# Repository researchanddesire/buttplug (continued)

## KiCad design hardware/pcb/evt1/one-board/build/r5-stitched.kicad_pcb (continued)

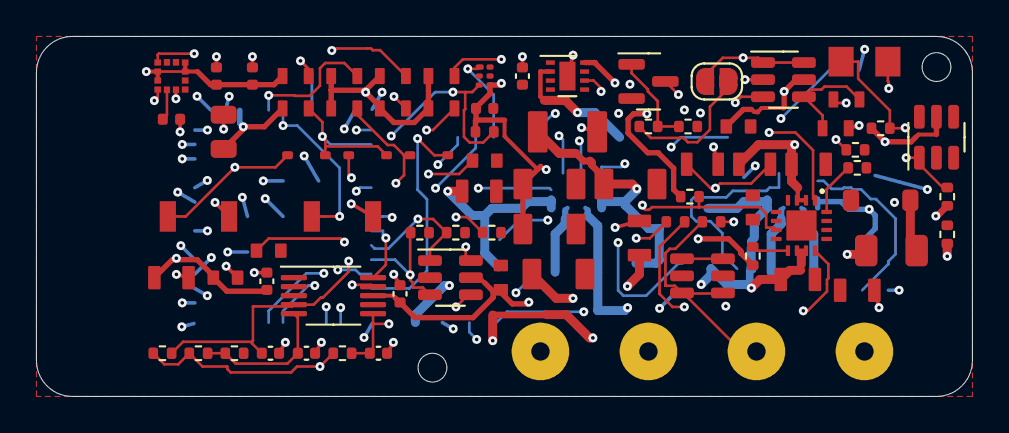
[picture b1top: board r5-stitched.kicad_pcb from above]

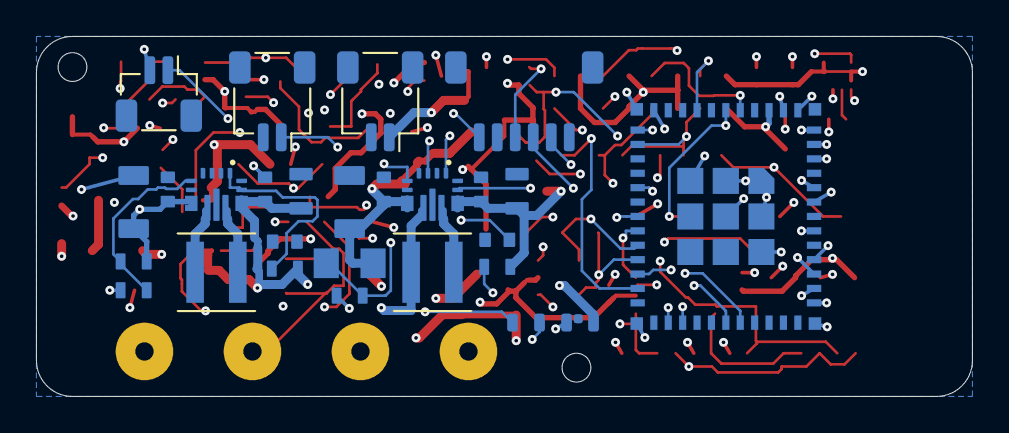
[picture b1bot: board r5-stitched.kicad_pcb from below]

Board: 4 copper layers, 52.0 x 20.0 mm, 110 parts (26 on the bottom side), 55 nets.

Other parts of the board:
J8: PACK MONITOR NTC / GND; JST_SH_SM02B-SRSS-TB_1x02-1MP_P1.00mm_Horizontal
MH1, MH3: PROVISIONAL M1.4 support

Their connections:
GND: J8.2; also elsewhere on the board
PACK_MON_NTC: J8.1; also elsewhere on the board

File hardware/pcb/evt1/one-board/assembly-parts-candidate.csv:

Comment,Designator,Footprint,Manufacturer Part Number,Baseline MPN
4.7uF 16V X7R,C1,Murata_GRM21_0805_Reflow,GRM21BR71C475KE51L,GRM21BR71A475KA73L
4.7uF 16V X7R,C2,Murata_GRM21_0805_Reflow,GRM21BR71C475KE51L,GRM21BR71A475KA73L
4.7uF 16V X7R,C3,Murata_GRM21_0805_Reflow,GRM21BR71C475KE51L,GRM21BR61A106KE19L
10uF 10V,C11,Murata_GRM21_0805_Reflow,GRM21BR61A106KE19L,GRM21BR61A106KE19L
22uF 10V X7R,C13,Murata_GRM31_1206_Reflow,GRM31CR71A226KE15L,GRM31CR71A226KE15L
22uF 10V X7R,C14,Murata_GRM31_1206_Reflow,GRM31CR71A226KE15L,GRM31CR71A226KE15L
22uF 10V X7R,C15,Murata_GRM31_1206_Reflow,GRM31CR71A226KE15L,GRM31CR71A226KE15L
100nF 10V,C16,Murata_GRM18_0603_Reflow,GRM188R71C104KA01D,GRM188R71C104KA01D
10uF 10V X5R 0603 HF,C51,TDK_C1608_0603_Reflow,CL10A106KP8NNNC,C1608X5R1A106K080AC
10uF 10V X5R 0603 HF,C52,TDK_C1608_0603_Reflow,CL10A106KP8NNNC,C1608X5R1A106K080AC
1.5uH / Isat>=4A candidate,L1,L_Coilcraft_XxL4020,XFL4020-152MEC,XFL4020-152MEC
8.87k 1% / ~100mA,R1,R_0402_1005Metric,TC0210B8871TCC,TNPW04028K87BEED
3.24k 1%,R2,R_0402_1005Metric,RT0402BRD073K24L,TNPW04023K24BEED
10k,R3,R_0402_1005Metric,TNPW040210K0BEED,TNPW040210K0BEED
10k,R4,R_0402_1005Metric,TNPW040210K0BEED,TNPW040210K0BEED
10k,R5,R_0402_1005Metric,TNPW040210K0BEED,TNPW040210K0BEED
312k 0.1%,R11,Vishay_TNPW0603_IEC_Reflow,RT0603BRD07312KL,TNPW0603312KBEEA
100k 0.1%,R12,Vishay_TNPW0603_IEC_Reflow,TNPW0603100KBEEA,TNPW0603100KBEEA
10k,R13,Vishay_TNPW0603_IEC_Reflow,TNPW060310K0BEEA,TNPW060310K0BEEA
BQ24074RGT candidate,U1,TI_RGT0016C_3x3mm_BQ24074_EP1.68mm,BQ24074RGTR,BQ24074RGTR
TPS63070RNM candidate,U2,TI_RNM0015A_2.5x3mm_TPS63070,TPS63070RNMR,TPS63070RNMR
10uF 10V,C31,Murata_GRM21_0805_Reflow,GRM21BR61A106KE19L,GRM21BR61A106KE19L
100nF,C32,Murata_GRM18_0603_Reflow,GRM188R71C104KA01D,GRM188R71C104KA01D
1uF,C33,TDK_C1608_0603_Reflow,CGA3E1X7R1V105KT000N,C1608X7R1E105K080AB
100nF,C34,Murata_GRM18_0603_Reflow,GRM188R71C104KA01D,GRM188R71C104KA01D
SERVICE_USB_BOOT,J4,JST_SH_SM06B-SRSS-TB_1x06-1MP_P1.00mm_Horizontal,SM06B-SRSS-TB(LF)(SN),SM06B-SRSS-TB(LF)(SN)
10k,R31,Vishay_TNPW0603_IEC_Reflow,TNPW060310K0BEEA,TNPW060310K0BEEA
10k,R32,Vishay_TNPW0603_IEC_Reflow,TNPW060310K0BEEA,TNPW060310K0BEEA
10k,R33,Vishay_TNPW0603_IEC_Reflow,TNPW060310K0BEEA,TNPW060310K0BEEA
10k,R34,Vishay_TNPW0603_IEC_Reflow,TNPW060310K0BEEA,TNPW060310K0BEEA
10k,R35,Vishay_TNPW0603_IEC_Reflow,TNPW060310K0BEEA,TNPW060310K0BEEA
10k,R36,Vishay_TNPW0603_IEC_Reflow,TNPW060310K0BEEA,TNPW060310K0BEEA
4.7k,R37,Vishay_TNPW0603_IEC_Reflow,TNPW06034K70BEEA,TNPW06034K70BEEA
4.7k,R38,Vishay_TNPW0603_IEC_Reflow,TNPW06034K70BEEA,TNPW06034K70BEEA
1.00M 1%,R39,Vishay_TNPW0805_IEC_Reflow,TNPW08051M00BEEA,TNPW08051M00BEEA
1.00M 1%,R40,Vishay_TNPW0805_IEC_Reflow,TNPW08051M00BEEA,TNPW08051M00BEEA
POWER / momentary,SW1,SW_SPST_B3U-1000P,B3U-1000P,B3U-1000P
MODE / momentary,SW2,SW_SPST_B3U-1000P,B3U-1000P,B3U-1000P
ESP32-C3-MINI-1-H4X,U6,Espressif_ESP32-C3-MINI-1_53Pads,ESP32-C3-MINI-1-H4X,ESP32-C3-MINI-1-N4X
100nF,C43,Murata_GRM18_0603_Reflow,GRM188R71C104KA01D,GRM188R71C104KA01D
100nF,C44,Murata_GRM18_0603_Reflow,GRM188R71C104KA01D,GRM188R71C104KA01D
AO3400A,Q1,SOT-23,AO3400A,AO3400A
10.0k 0.1%,R42,R_0402_1005Metric,TNPW040210K0BEED,TNPW040210K0BEED
715k 0.1%,R43,RESI_PTFR0805_C16003,PTFR0805B715KP9,TNPW0805715KBEEA
110k 0.1%,R44,Vishay_TNPW0603_IEC_Reflow,TNPW0603110KBEEA,TNPW0603110KBEEA
200k 0.1%,R45,Vishay_TNPW0603_IEC_Reflow,ERA3AEB204V,TNPW0603200KBEEA
11k 1%,R46,R_0402_1005Metric,RT0402BRD0711KL,TNPW040211K0BEED
1k 1%,R47,R_0402_1005Metric,TNPW04021K00BEED,TNPW04021K00BEED
100k 1%,R48,R_0402_1005Metric,TNPW0402100KBEED,TNPW0402100KBEED
TPS3700DDCR,U8,TSOT-23-6,TPS3700DDCR,TPS3700DDCR
TPS3808G33QDBVRQ1,U9,SOT-23-6,TPS3808G33QDBVRQ1,TPS3808G33DBVR
100nF,C71,C_0402_1005Metric,GRM155R71C104KA88D,GRM155R71C104KA88D
BAT54WS-E3-08,D71,D_SOD-323,BAT54WS-E3-08,BAT54WS-E3-08
BAT54WS-E3-08,D72,D_SOD-323,BAT54WS-E3-08,BAT54WS-E3-08
BAT54WS-E3-08,D73,D_SOD-323,BAT54WS-E3-08,BAT54WS-E3-08
10k,R71,R_0402_1005Metric,TNPW040210K0BEED,TNPW040210K0BEED
TPS3422EGDRYR,U71,Texas_USON-6_1x1.45mm_P0.5mm_SMD,TPS3422EGDRYR,TPS3422EGDRYR
10uF 10V,C21,Murata_GRM21_0805_Reflow,GRM21BR61A106KE19L,GRM21BR61A106KE19L
22uF 10V X7R,C23,Murata_GRM31_1206_Reflow,GRM31CR71A226KE15L,GRM31CR71A226KE15L
22uF 10V X7R,C24,Murata_GRM31_1206_Reflow,GRM31CR71A226KE15L,GRM31CR71A226KE15L
22uF 10V X7R,C25,Murata_GRM31_1206_Reflow,GRM31CR71A226KE15L,GRM31CR71A226KE15L
100nF 10V,C26,Murata_GRM18_0603_Reflow,GRM188R71C104KA01D,GRM188R71C104KA01D
100nF,C27,Murata_GRM18_0603_Reflow,GRM188R71C104KA01D,GRM188R71C104KA01D
100nF,C28,C_0402_1005Metric,GRM155R71C104KA88D,GRM155R71C104KA88D
100nF,C29,C_0402_1005Metric,GRM155R71C104KA88D,GRM155R71C104KA88D
47uF 10V,C30,Murata_GRM32_1210_Reflow,GRM32ER61A476KE20L,GRM32ER61A476KE20L
10uF 10V X5R 0603 HF,C53,TDK_C1608_0603_Reflow,CL10A106KP8NNNC,C1608X5R1A106K080AC
10uF 10V X5R 0603 HF,C54,TDK_C1608_0603_Reflow,CL10A106KP8NNNC,C1608X5R1A106K080AC
MOTOR_2PIN,J3,JST_SH_SM02B-SRSS-TB_1x02-1MP_P1.00mm_Horizontal,SM02B-SRSS-TB(LF)(SN),SM02B-SRSS-TB(LF)(SN)
1.5uH / Isat>=4A candidate,L2,L_Coilcraft_XxL4020,XFL4020-152MEC,XFL4020-152MEC
360k 0.1%,R21,RESI_PTFR0805_C16003,PTFR0805B360KN9,TNPW0805362KBEEA
100k 0.1%,R22,Vishay_TNPW0603_IEC_Reflow,TNPW0603100KBEEA,TNPW0603100KBEEA
100k,R23,R_0402_1005Metric,TNPW0402100KBEED,TNPW0402100KBEED
100k,R24,R_0402_1005Metric,TNPW0402100KBEED,TNPW0402100KBEED
100k,R25,R_0402_1005Metric,TNPW0402100KBEED,TNPW0402100KBEED
10k,R26,Vishay_TNPW0603_IEC_Reflow,TNPW060310K0BEEA,TNPW060310K0BEEA
TPS63070RNM candidate,U3,TI_RNM0015A_2.5x3mm_TPS63070,TPS63070RNMR,TPS63070RNMR
SN74LVC1G11DBV candidate,U4,SOT-23-6,SN74LVC1G11DBVR,SN74LVC1G11DBVR
DRV8212DSG candidate,U5,WSON-8-1EP_2x2mm_P0.5mm_EP0.9x1.6mm,DRV8212DSGR,DRV8212DSGR
100nF,C61,C_0402_1005Metric,GRM155R71C104KA88D,GRM155R71C104KA88D
10nF,C62,C_0402_1005Metric,GRM155R71H103KA88D,GRM155R71H103KA88D
10nF,C63,C_0402_1005Metric,GRM155R71H103KA88D,GRM155R71H103KA88D
10nF 50V X7R,C88,C_0402_1005Metric,GRM155R71H103KA88D,
TIP NTC / GND,J5,JST_SH_BM02B-SRSS-TB_1x02-1MP_P1.00mm_Vertical,BM02B-SRSS-TB(LF)(SN),BM02B-SRSS-TB(LF)(SN)
PACK MONITOR NTC / GND,J8,JST_SH_SM02B-SRSS-TB_1x02-1MP_P1.00mm_Horizontal,SM02B-SRSS-TB(LF)(SN),
10k 0.1%,R61,R_0402_1005Metric,TNPW040210K0BEED,TNPW040210K0BEED
10k 0.1%,R62,R_0402_1005Metric,TNPW040210K0BEED,TNPW040210K0BEED
10k 0.1%,R63,R_0402_1005Metric,TNPW040210K0BEED,TNPW040210K0BEED
10k 0.1%,R88,R_0402_1005Metric,TNPW040210K0BEED,
ADS1115IDGSR /0x48,U7,VSSOP-10_3x3mm_P0.5mm,ADS1115IDGSR,ADS1115IDGSR
Schottky 1A/20V candidate,D1,Diodes_B140HW_SOD123_A1_K2,B140HW-7,B140HW-7
PTC 500mA candidate,F1,Fuse_1206_3216Metric,1206L050YR,1206L050YR
22R,R75,R_0402_1005Metric,RC0402FR-0722RL,TNPW040222R0BEED
22R,R76,R_0402_1005Metric,RC0402FR-0722RL,TNPW040222R0BEED
USBLC6-2SC6,U75,SOT-23-6,USBLC6-2SC6,USBLC6-2SC6
220nF,C81,C_0402_1005Metric,GRM155R71C224KA12D,GRM155R71C224KA12D
100nF,C82,C_0402_1005Metric,GRM155R71C104KA88D,GRM155R71C104KA88D
47uF 10V / Ceff>=10uF at3V3,C83,C_0805_2012Metric,MSASL21GBB5476MTNA01,C2012X5R1E226M125AC
100nF / VDDIO local,C84,C_0402_1005Metric,GRM155R71C104KA88D,GRM155R71C104KA88D
LSM303AGRTR,U81,LGA-12_2x2mm_P0.5mm,LSM303AGRTR,LSM303AGRTR

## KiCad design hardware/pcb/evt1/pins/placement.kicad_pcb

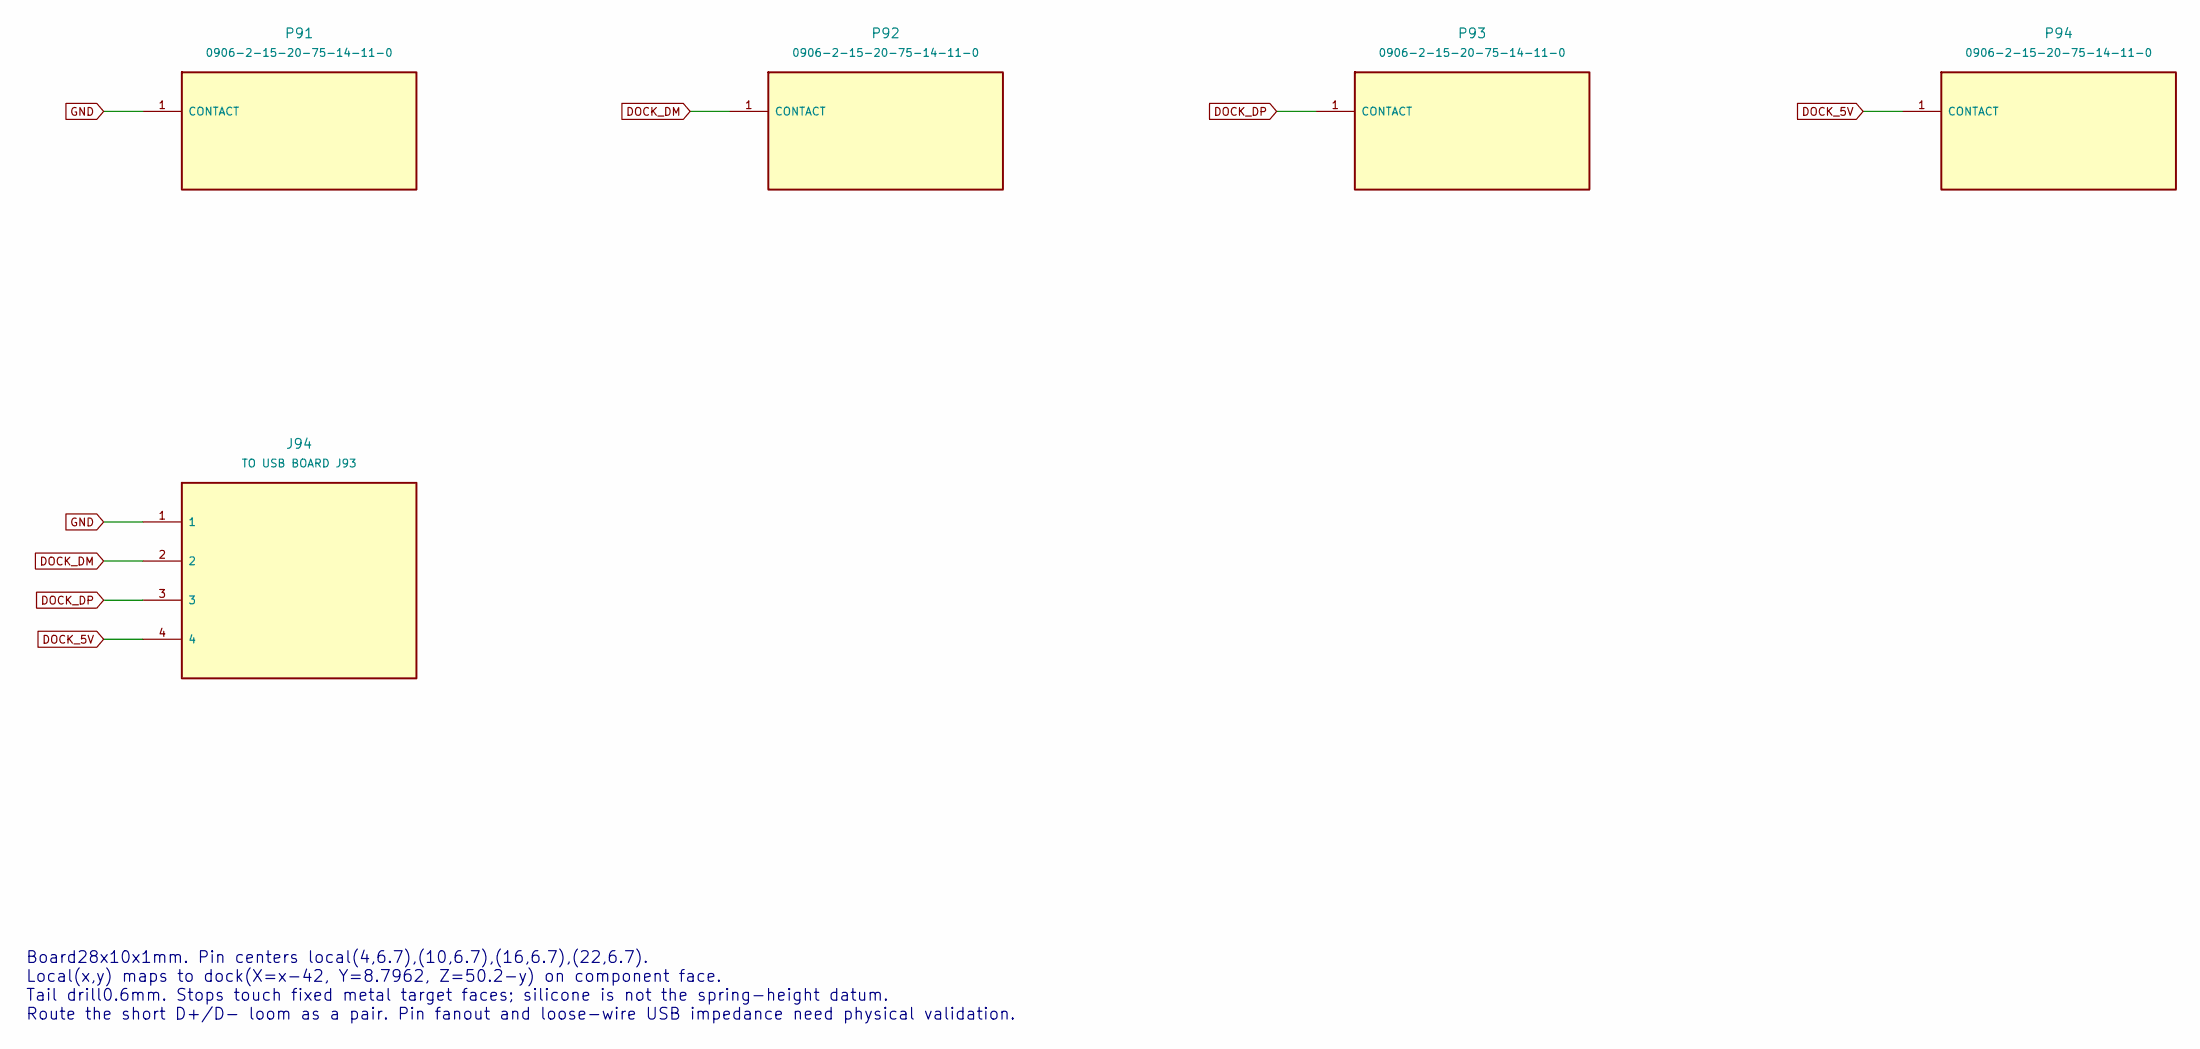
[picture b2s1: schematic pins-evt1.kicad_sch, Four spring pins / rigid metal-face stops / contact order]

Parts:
J94: TO USB BOARD J93; Contact_Loom_4Land
P91, P92, P93, P94: 0906-2-15-20-75-14-11-0; MillMax_0906_2

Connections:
DOCK_5V: J94.4, P94.1
DOCK_DM: J94.2, P92.1
DOCK_DP: J94.3, P93.1
GND: J94.1, P91.1

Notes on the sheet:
Board28x10x1mm. Pin centers local(4,6.7),(10,6.7),(16,6.7),(22,6.7). Local(x,y) maps to dock(X=x-42, Y=8.7962, Z=50.2-y) on component face. Tail drill0.6mm. Stops touch fixed metal target faces; silicone is not the spring-height datum. Route the short D+/D- loom as a pair. Pin fanout and loose-wire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

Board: 2 copper layers, 5 parts (1 on the bottom side), 4 nets, no tracks yet.

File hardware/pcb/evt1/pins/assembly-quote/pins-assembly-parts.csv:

Manufacturer,MPN,Quantity_per_board,References,Schematic_value,Footprint,Assembly_note,Manufacturer_source
Mill-Max,0906-2-15-20-75-14-11-0,4,P91 P92 P93 P94,0906-2-15-20-75-14-11-0,EVT1:MillMax_0906_2,"Spring pin through1mm board; height/stroke are set by the carrier/retainer, not a generic component-height box.",https://www.mill-max.com/products/spring-loaded/0906

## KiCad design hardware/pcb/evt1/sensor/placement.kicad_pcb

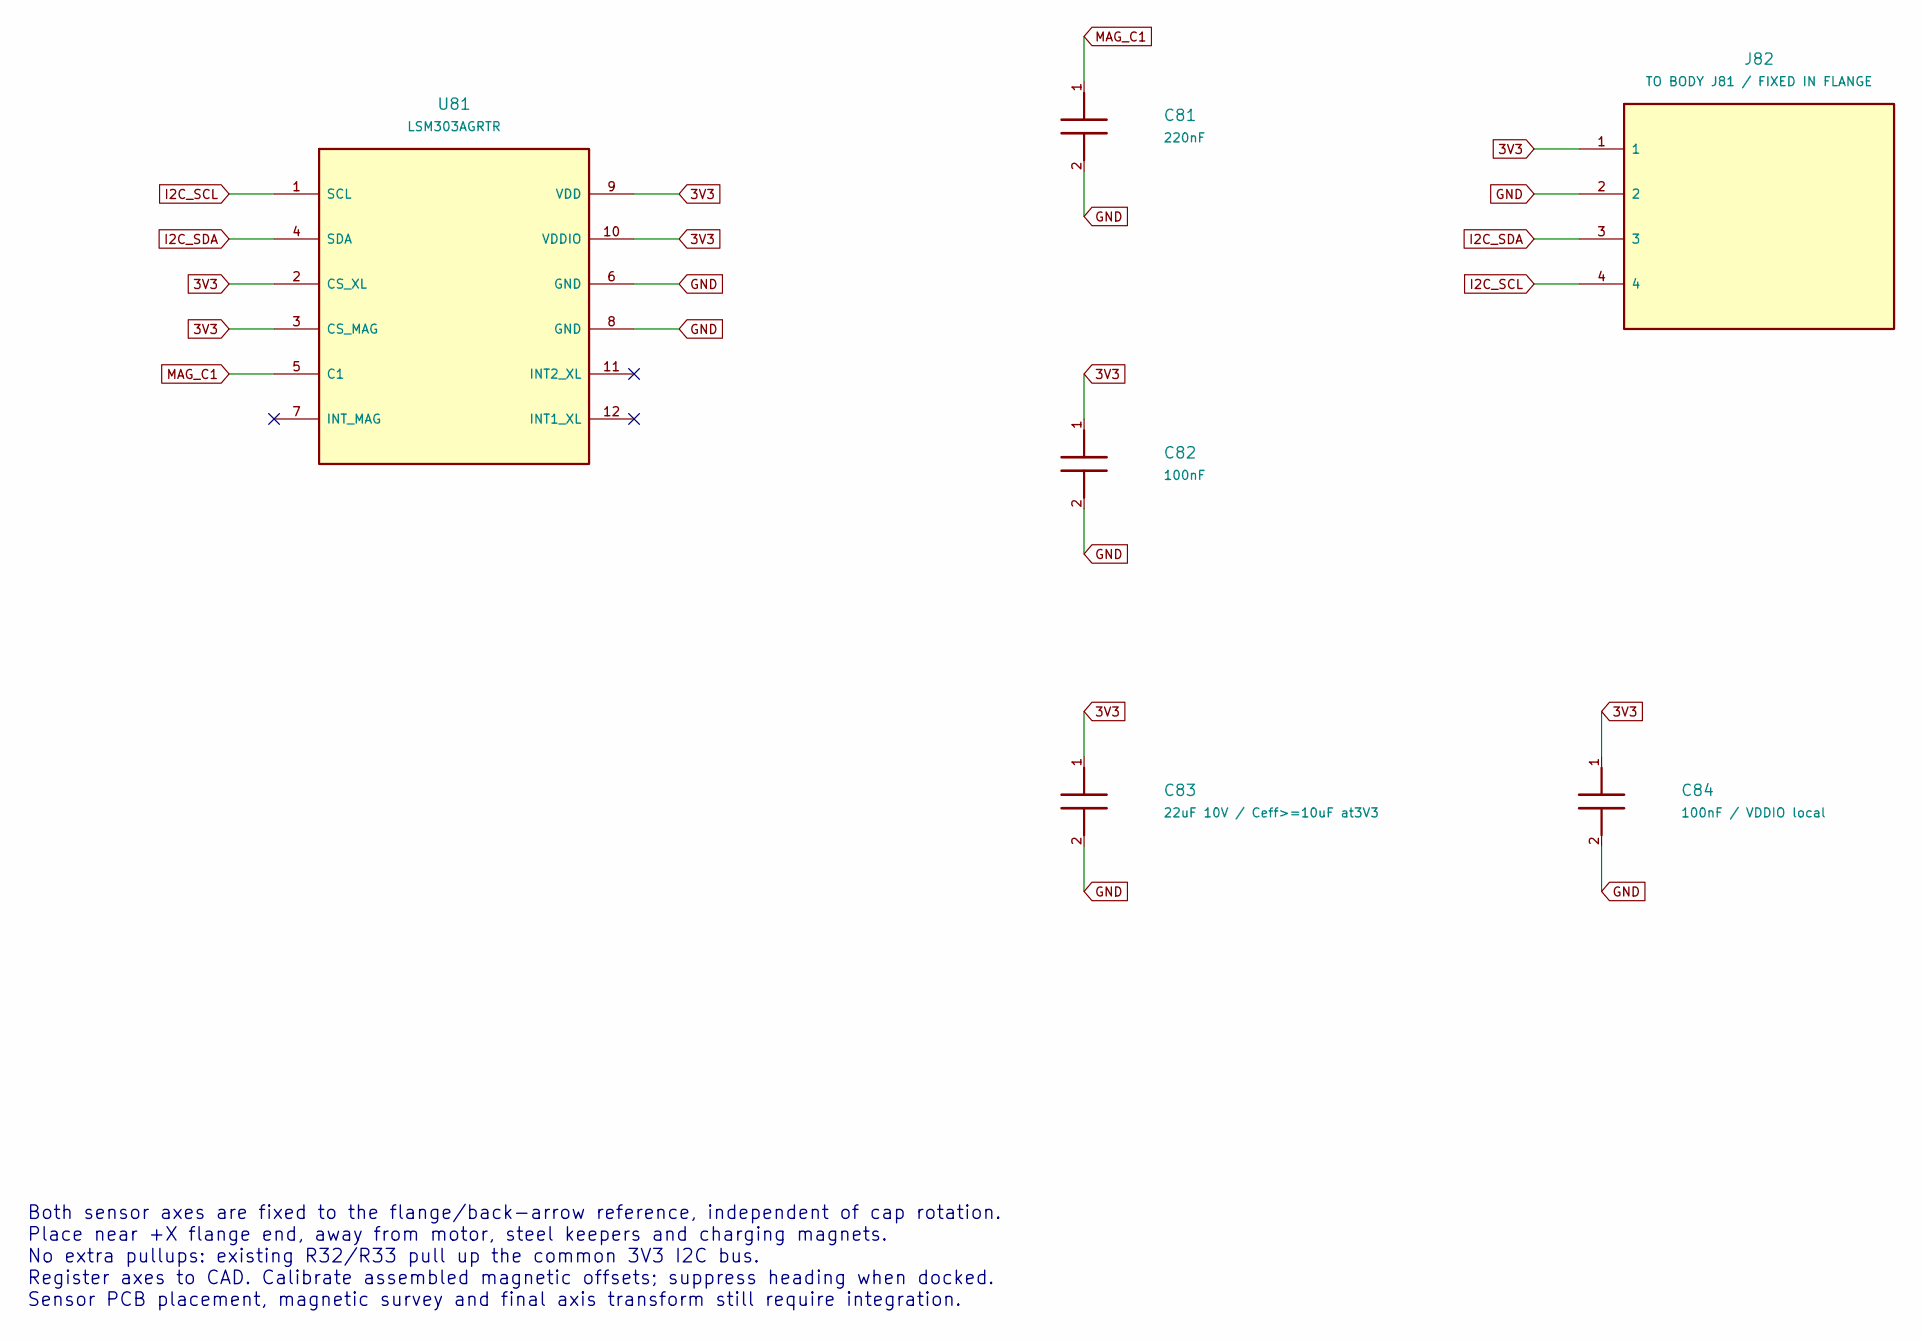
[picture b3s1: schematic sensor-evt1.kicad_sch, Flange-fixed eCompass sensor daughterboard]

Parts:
C81: 220nF; C_0402_1005Metric
C82: 100nF; C_0402_1005Metric
C83: 22uF 10V / Ceff>=10uF at3V3; C_0805_2012Metric
C84: 100nF / VDDIO local; C_0402_1005Metric
J82: TO BODY J81 / FIXED IN FLANGE; Sensor_Loom_4Land
U81: LSM303AGRTR; LGA-12_2x2mm_P0.5mm

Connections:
3V3: C82.1, C83.1, C84.1, J82.1, U81.2 (CS_XL), U81.3 (CS_MAG), U81.9 (VDD), U81.10 (VDDIO)
GND: C81.2, C82.2, C83.2, C84.2, J82.2, U81.6 (GND), U81.8 (GND)
I2C_SCL: J82.4, U81.1 (SCL)
I2C_SDA: J82.3, U81.4 (SDA)
MAG_C1: C81.1, U81.5 (C1)

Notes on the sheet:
Both sensor axes are fixed to the flange/back-arrow reference, independent of cap rotation. Place near +X flange end, away from motor, steel keepers and charging magnets. No extra pullups: existing R32/R33 pull up the common 3V3 I2C bus. Register axes to CAD. Calibrate assembled magnetic offsets; s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

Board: 2 copper layers, 8 parts (0 on the bottom side), 5 nets, no tracks yet.

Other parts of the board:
H1, H2: NPTH_1.6mm_LocatingPin
